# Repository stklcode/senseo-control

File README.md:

View this project on [CADLAB.io](https://cadlab.io/node/863). 

# Senseo Control 2.0 

A completely rebuilt AVR based hard- and software for Senseo® HD782x coffee machine.
It allows custom setting of cup size and temperature and includes simple support for a second cup size (e.g. espresso) by pushing the buttons longer (2s).

The original project was documented in [this blog post](https://www.stklblog.de/blog/senseo-control-20) (German), including photos of the prototype.

## Functionality

The OEM functionality (coffee, rinsing, auto-off) has been reimplemented (indications adapted to RGB LED) with a few features on top. 

### Features

|         |  Input                           | Action                                               |
|:-------:|:--------------------------------:|:----------------------------------------------------:|
| ⬤ ⭗ ⬤ | push both coffee buttons         | rinsing cycle (pump cold water, until tank is empty) |
| ⬤ ⭗ ⭕ | push single coffee button        | 1/2 cups of coffee                                   |
| ⬤ ⭗ ⭕ | push single coffee button for 2s | 1/2 cups of espresso (shorter time, 2s pre-brewing)  |
| ⭕ ⬤ ⭕ | push power button                | start / shutdown at any time                         |
| ⭕ ⭗ ⭕ | 3 minutes idle                   | Auto-Off                                             |

#### Optional Features

* **Coffee wish** - if enabled (see below), the machine will memorize your coffee wish during heat-up and automatically 
start the coffee when finished, indicating through a violet LED (instead of green) 

### LED Signals

| Color  | Light                                      | Flashing                                                     |
|:------:|:------------------------------------------:|:------------------------------------------------------------:|
| red    | -                                          | <span style="color:red">◍</span> heating up                  |
| green  | <span style="color:green">⬤</span> ready  | <span style="color:green">◍</span> coffee running            |
| orange | -                                          | <span style="color:orange">◍</span> espresso running         |
| blue   | <span style="color:blue">⬤</span> rinsing | <span style="color:blue">◍</span> water empty                |
| violet | -                                          | <span style="color:violet">◍</span> heating up (coffee wish) |

## Platform

### Hardware

The hardware is based on an **ATtiny26** microcontroller with internal 8MHz RC oscillator.

Power supply is provided by a small transforer with a _78L05_ linear regulator. 
Pump and boiler are controlled by Triacs with isolated MOC30xx drivers.
The original sensors (NTC for temperature, Hall for water tank switch) are directly attached to the new board.

### Schematic and Layout

The prototype has been built in THT on a perfboard, hence the layout provided is compatible to 2.54mm (100mil) grid.
Might as well be used for a PCB. The board is designed to fit the HD7822 model.

Files provided under _hardware/_ are compatible with CadSoft/Autodesk EAGLE™ 6 and above.

### Firmware

The firmware is written in _C_ and comes with a _Makefile_ for use with _avr-gcc_ and _avrdude_.
There are configurations available for _STK500_, _AVR ISP mkII_ and _Pony-STK200_ which can be adapted to your setup.

## Customization

The code is designed to customize functions, timing, temperature and hardware pinning.
To to so, set the corresponding fields in the _main.h_ file:

| Flag                    | Default | Description                                  |
|-------------------------|---------|----------------------------------------------|
| `TIME_1_ESPRESSO`       | 15      | pump time 1 espresso (seconds)               |
| `TIME_2_ESPRESSO`       | 28      | pump time 2 espressos (seconds)              |
| `TIME_1_COFFEE`         | 26      | pump time 1 coffee (seconds)                 |
| `TIME_2_COFFEE`         | 52      | pump time 2 coffees (seconds)                |
| `OPERATING_TEMPERATURE` | 125     | water temperature (ADC value)                |
| `AUTO_OFF_THRESHOLD`    | 180     | Auto-Off time (seconds  after last action)   |
| `COFFEE_WISH`           | 0       | save coffee wish on heat-up (`1` to enable)  |

Pinout, button-thresholds and LED-configuration is also present in this file (should be self-explaining).

## Build Instructions
* Required tools: _avr-gcc_, _avr-objcopy_, _avrdude_ (for flashing only), _make_
* All sources are bundled in the `firmware` directory
* Check `Makefile.config` for the correct settings, especially tool and port for automated flashing.
* On first build you might want to set the correct fuse bits, so run `make fuses`
* Run `make compile info program` for compilation, details about binary, and flashing
* Check `make help` for all available commands

## Notes

The Triacs need heatsink.
The prototype uses approx. 75 x 30 x 1.5 mm (3 x 1.2 x 0.06 in) aluminum sheet, which is about the minimum recommended with a maximum temperature around 70°C (158°F).

<span style="background-color:lightyellow;padding:.5em;border-left:4px orange solid;display:block">**⚡ Danger - High Voltage ⚡**<br>
Working on a live coffee machine involves voltages of 120/230V AC **!** This voltage is applied to the heatsinks and causes hazard on contact.<br>
Please make sure you know what you are doing or consult an authorized professional.<br>
<br>
Cut the power before working on the device.
First tests can be done without main power (supply the µC with 5V from the programmer), Triacs can be tested with low voltage (e.g. 12V~).
On final test use an isolating transformer or at least a RCD.</span>

## License

The project is licensed under [GPL v3](https://www.gnu.org/licenses/gpl-3.0.de.html) license.

## Disclaimer

_"SENSEO"_ is a Trademark of _Koninklijke Philips N.V._ when used for coffee makers and a Trademark of _Sara Lee/De N.V._ when used for coffee pods.
No claim is made to the exclusive right to use _Senseo_ apart from the mark as shown.

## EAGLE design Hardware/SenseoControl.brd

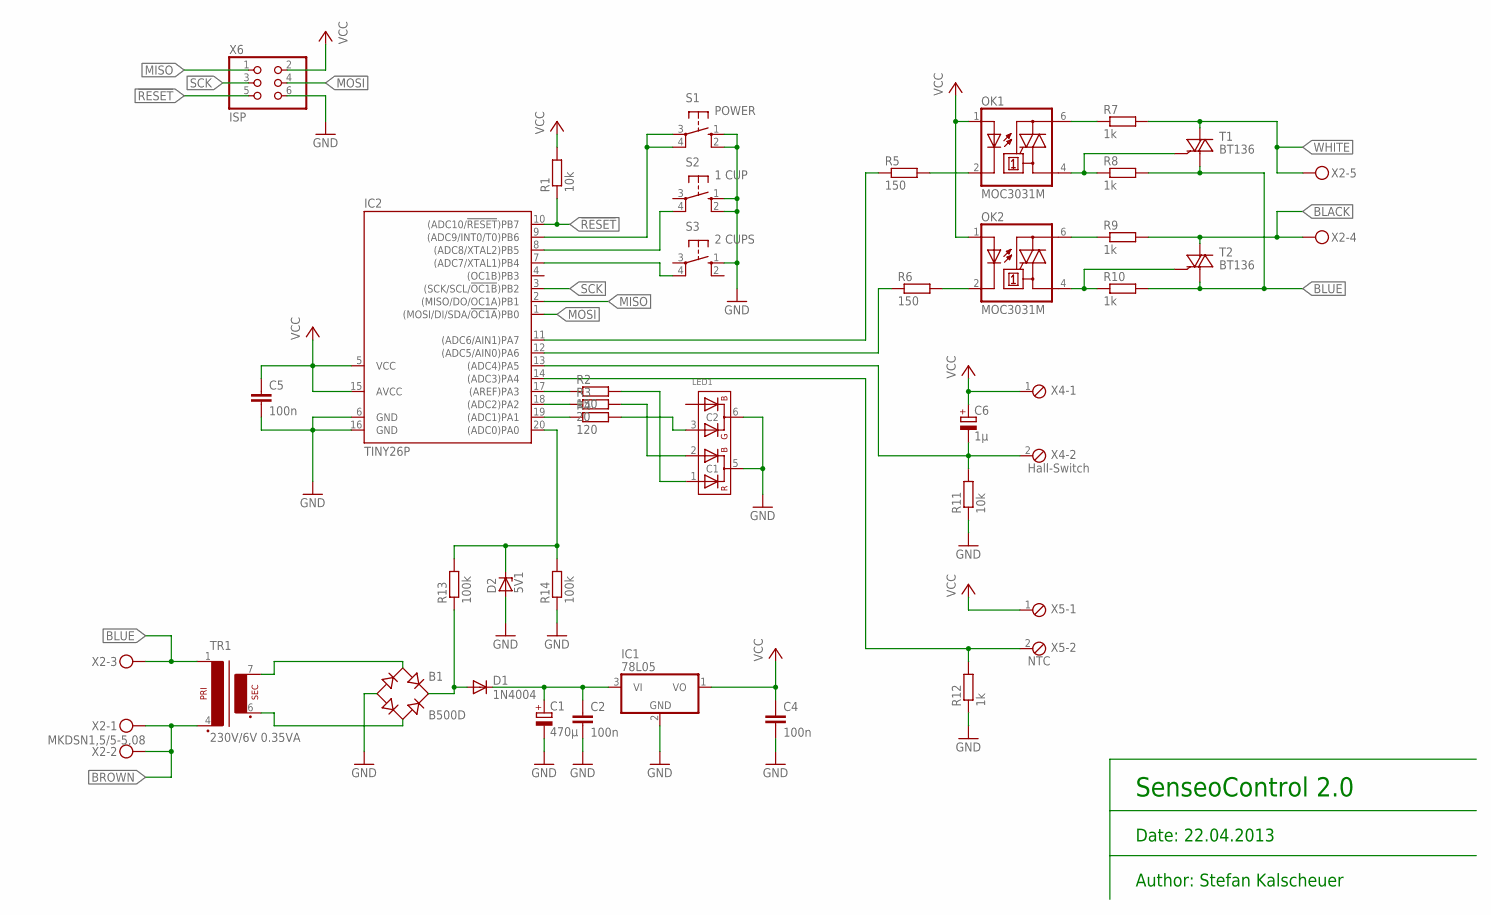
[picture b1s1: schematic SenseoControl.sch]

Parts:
B1: B500D; B-DIL
C1: 470µ; E2,5-6
C2, C4, C5: 100n; C025-024X044
C6: 1µ; TT2D5
D1: 1N4004; D-2.5
D2: 5V1; ZDIO-7.5
IC1: 78L05; TO92-A
IC2: TINY26P; DIL20
LED1: LF5
OK1, OK2: MOC3031M; DIL06
R1: 10k; 0207/12
R2, R5, R6: 150; 0204/7
R3: 20; 0204/7
R4: 120; 0204/7
R7, R8, R9, R10, R12: 1k; 0204/7
R11: 10k; 0204/7
R13, R14: 100k; 0204/7
S1: POWER; B3F-10XX-A
S2: 1 CUP; B3F-10XX-A
S3: 2 CUPS; B3F-10XX-A
T1, T2: BT136; TO220AB
TR1: 230V/6V 0.35VA; EE20-1
X2: MKDSN1,5/5-5,08
X4: Hall-Switch; 2POL254
X5: NTC; 2POL254
X6: ISP; 2X03

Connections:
!RESET: IC2.10 ((ADC10/!RESET!)PB7), R1.1, X6.5
BLACK: R9.2, T2.2 (A2), X2.4
BLUE: R8.2, R10.2, T1.1 (A1), T2.1 (A1), TR1.1, X2.3
BROWN: TR1.4 (P2), X2.1, X2.2
GND: B1.-, C1.-, C2.2, C4.2, C5.2, D2.A, IC1.2 (GND), IC2.6 (GND), IC2.16 (GND), LED1.5 (C1), LED1.6 (C2), R11.1, R12.1, R14.1, S1.1 (S), S1.2 (S1), S2.1 (S), S2.2 (S1), S3.1 (S), X6.6
MISO: IC2.2 ((MISO/DO/OC1A)PB1), X6.1
MOSI: IC2.1 ((MOSI/DI/SDA/!OC1A!)PB0), X6.4
unnamed: LED1.2 (A-BLUE), R3.2
unnamed: B1.AC1, TR1.7 (S4)
unnamed: OK1.4 (A1), R8.1, T1.3 (G)
unnamed: B1.AC2, TR1.6 (S3)
unnamed: IC2.18 ((ADC2)PA2), R3.1
unnamed: D2.C, IC2.20 ((ADC0)PA0), R13.2, R14.2
unnamed: C1.+, C2.1, D1.C, IC1.3 (VI)
unnamed: IC2.7 ((ADC7/XTAL1)PB4), S3.4 (P1)
unnamed: IC2.8 ((ADC8/XTAL2)PB5), S2.4 (P1)
unnamed: IC2.9 ((ADC9/INT0/T0)PB6), S1.3, S1.4 (P1)
unnamed: IC2.17 ((AREF)PA3), R2.1
unnamed: LED1.3 (A_GREEN), R4.2
unnamed: LED1.1 (A-RED), R2.2
unnamed: B1.+, D1.A, R13.1
unnamed: IC2.19 ((ADC1)PA1), R4.1
unnamed: IC2.11 ((ADC6/AIN1)PA7), R5.1
unnamed: IC2.12 ((ADC5/AIN0)PA6), R6.1
unnamed: OK1.6 (A2), R7.1
unnamed: OK2.6 (A2), R9.1
unnamed: OK2.4 (A1), R10.1, T2.3 (G)
unnamed: OK2.2 (C), R6.2
unnamed: OK1.2 (C), R5.2
unnamed: C6.-, IC2.13 ((ADC4)PA5), R11.2, X4.2
unnamed: IC2.14 ((ADC3)PA4), R12.2, X5.2
SCK: IC2.3 ((SCK/SCL/!OC1B!)PB2), X6.3
VCC: C4.1, C5.1, C6.+, IC1.1 (VO), IC2.5 (VCC), IC2.15 (AVCC), OK1.1 (A), OK2.1 (A), R1.2, X4.1, X5.1, X6.2
WHITE: R7.2, T1.2 (A2), X2.5

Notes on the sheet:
SenseoControl 2.0
Author: Stefan Kalscheuer
Date: 22.04.2013

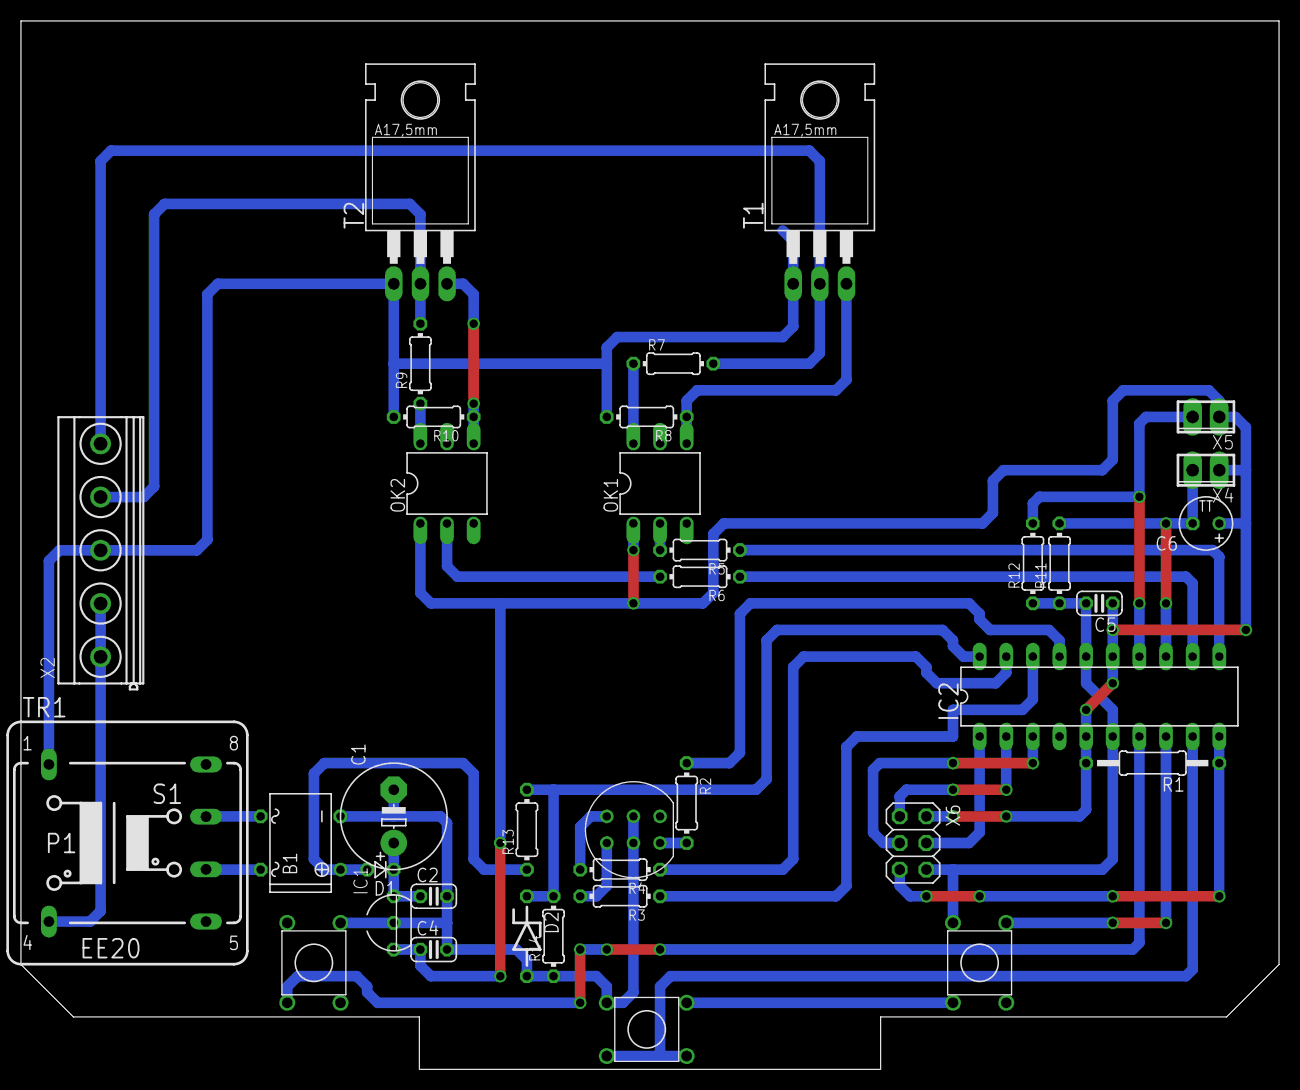
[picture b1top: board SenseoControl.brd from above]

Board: 2 copper layers, 120.0 x 100.0 mm, 37 parts (0 on the bottom side), 34 nets.

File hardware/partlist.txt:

Partlist

Exported from SenseoControl 2.0

Part     Value           Device            Package         Library         Sheet

B1       B500D           B-DIL             B-DIL           rectifier       1
C1       470µ            CPOL-EUE2.5-6     E2,5-6          resistor        1
C2       100n            C-EU025-024X044   C025-024X044    resistor        1
C4       100n            C-EU025-024X044   C025-024X044    resistor        1
C5       100n            C-EU025-024X044   C025-024X044    resistor        1
C6       1µ              CPOL-EUTT2D5      TT2D5           resistor        1
D1       1N4004          DIODE-D-2.5       D-2.5           diode           1
D2       5V1             ZENER-DIODEZD-7.5 ZDIO-7.5        diode           1
IC1      78L05           78L2              TO92-A          linear          1
IC2      TINY26P         TINY26P           DIL20           atmel           1
LED1     LF5             LF5               LF5             led-rgb         1
OK1      MOC3031M        MOC3031M          DIL06           optocoupler     1
OK2      MOC3031M        MOC3031M          DIL06           optocoupler     1
R1       10k             R-EU_0207/12      0207/12         resistor        1
R2       150             R-EU_0204/7       0204/7          resistor        1
R3       20              R-EU_0204/7       0204/7          resistor        1
R4       120             R-EU_0204/7       0204/7          resistor        1
R5       150             R-EU_0204/7       0204/7          resistor        1
R6       150             R-EU_0204/7       0204/7          resistor        1
R7       1k              R-EU_0204/7       0204/7          resistor        1
R8       1k              R-EU_0204/7       0204/7          resistor        1
R9       1k              R-EU_0204/7       0204/7          resistor        1
R10      1k              R-EU_0204/7       0204/7          resistor        1
R11      10k             R-EU_0204/7       0204/7          resistor        1
R12      1k              R-EU_0204/7       0204/7          resistor        1
R13      100k            R-EU_0204/7       0204/7          resistor        1
R14      100k            R-EU_0204/7       0204/7          resistor        1
S1       POWER           10-XXA            B3F-10XX-A      switch-omron    1
S2       1 CUP           10-XXA            B3F-10XX-A      switch-omron    1
S3       2 CUPS          10-XXA            B3F-10XX-A      switch-omron    1
T1       BT136           BT136             TO220AB         triac           1
T2       BT136           BT136             TO220AB         triac           1
TR1      230V/6V 0.35VA  EE20-1            EE20-1          trafo           1
X2       MKDSN1,5/5-5,08 MKDSN1,5/5-5,08   MKDSN1,5/5-5,08 con-phoenix-508 1
X4       Hall-Switch     MPT2              2POL254         con-phoenix-254 1
X5       NTC             MPT2              2POL254         con-phoenix-254 1
X6       ISP             PINHD-2X3         2X03            pinhead         1

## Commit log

2017-07-03 Imported from SVN
2017-07-04 Code reformatted
    Constants for pump times in main.h (more readable code, easier to adjust)
2017-07-04 Coffee wish implemented with violet led indicator
2017-07-04 Defined constant flags for LED colors
2017-07-04 Schematic and layout added
2017-07-04 ReadMe, Partlist, minor restructuring
2017-07-04 .gitignore
2018-04-11 Backlink to CADLAB.io has been added.
2022-11-23 Copyright + License; reformatting
2022-11-23 Separated Makefile and config; added build instructions
2022-11-23 Switched to size optimization
2022-11-23 Bundled boolean flags into single 8bit mask
2022-11-23 Replaced 5 step if-else by switch-case
2022-11-23 minor code cleanup
2022-11-23 define coffee flags as pre-processor macros
    Right now we need at least some knowledge about the values 0-4
    representing five possible states of coffee making. Make it readable
    without this knowledge.
2022-11-23 extract button processing and coffee/cleaning routines into functions
2022-12-18 add Drone CI configuration to build firmware
2025-02-02 migrate Drone CI workflow to GitHub Actions
